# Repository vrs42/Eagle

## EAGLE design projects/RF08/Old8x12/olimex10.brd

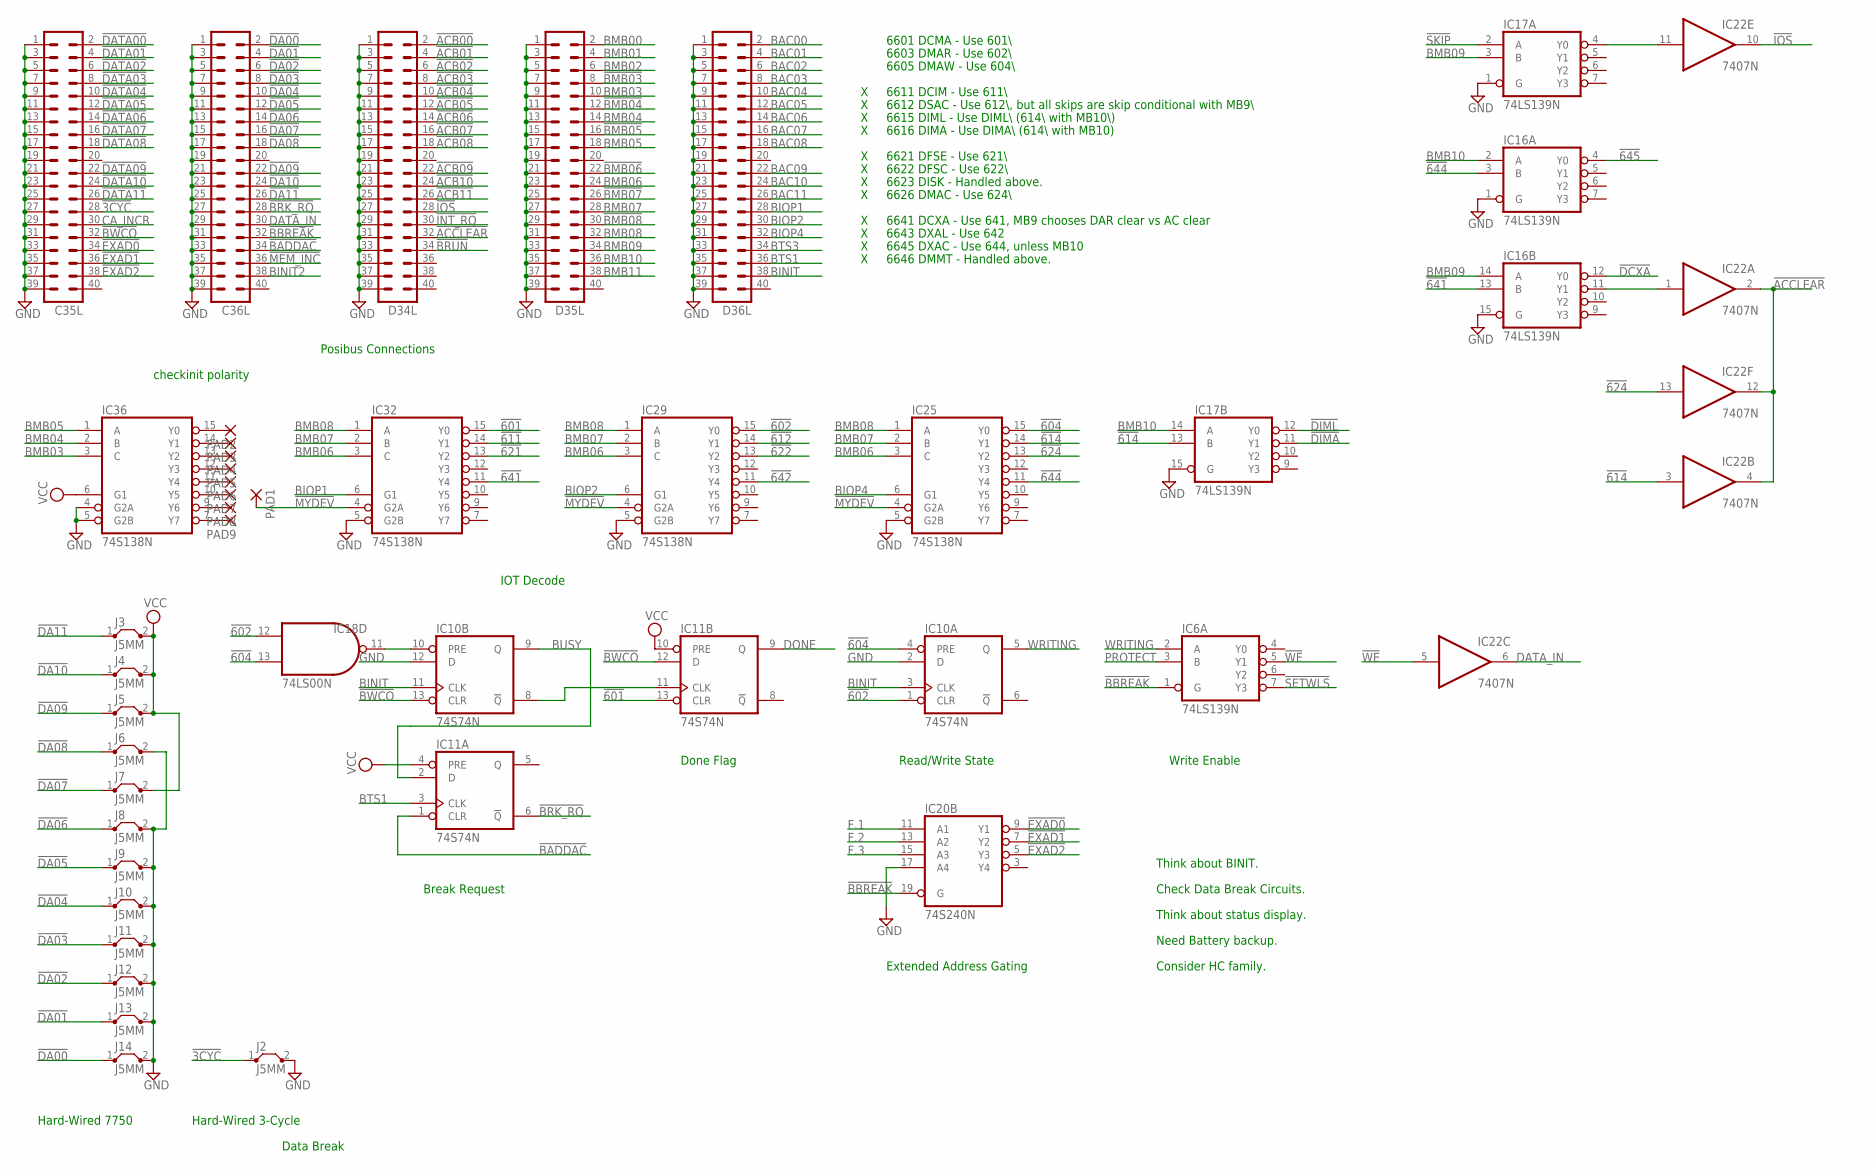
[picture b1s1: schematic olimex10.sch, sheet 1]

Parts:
C35L, C36L: MA20-2
D34L, D35L, D36L: MA20-2
IC6, IC16, IC17: 74LS139N; DIL16
IC10, IC11: 74S74N; DIL14
IC18: 74LS00N; DIL14
IC20: 74S240N; DIL20
IC22: 7407N; DIL14
IC25, IC29, IC32, IC36: 74S138N; DIL16
J2, J3, J4, J5, J6, J7, J8, J9, J10, J11, J12, J13, J14: J5MM; 05
PAD1, PAD2, PAD3, PAD4, PAD5, PAD6, PAD7, PAD8, PAD9: 1,6/0,8

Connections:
!3CYC: C35L.28, J2.1
!601: IC11.13 (CLR), IC32.15 (Y0); also elsewhere on the board
!602: IC10.1 (CLR), IC18.12 (I0), IC29.15 (Y0); also elsewhere on the board
!604: IC10.4 (PRE), IC18.13 (I1), IC25.15 (Y0); also elsewhere on the board
!611: IC32.14 (Y1); also elsewhere on the board
!612: IC29.14 (Y1); also elsewhere on the board
!614: IC17.13 (B), IC22.3 (I), IC25.14 (Y1)
!621: IC32.13 (Y2); also elsewhere on the board
!622: IC29.13 (Y2); also elsewhere on the board
!624: IC22.13 (I), IC25.13 (Y2); also elsewhere on the board
!641: IC16.13 (B), IC32.11 (Y4)
!642: IC29.11 (Y4); also elsewhere on the board
!644: IC16.3 (B), IC25.11 (Y4)
!645: IC16.4 (Y0); also elsewhere on the board
!ACB00: D34L.2; also elsewhere on the board
!ACB01: D34L.4; also elsewhere on the board
!ACB02: D34L.6; also elsewhere on the board
!ACB03: D34L.8; also elsewhere on the board
!ACB04: D34L.10; also elsewhere on the board
!ACB05: D34L.12; also elsewhere on the board
!ACB06: D34L.14; also elsewhere on the board
!ACB07: D34L.16; also elsewhere on the board
!ACB08: D34L.18; also elsewhere on the board
!ACB09: D34L.22; also elsewhere on the board
!ACB10: D34L.24; also elsewhere on the board
!ACB11: D34L.26; also elsewhere on the board
!ACCLEAR: D34L.32, IC22.2 (O), IC22.4 (O), IC22.12 (O)
!BADDAC: C36L.34, IC11.1 (CLR)
!BBREAK: C36L.32, IC6.1 (G), IC20.19 (G); also elsewhere on the board
!BMB03: D35L.8
!BMB04: D35L.12
!BMB05: D35L.16
!BMB06: D35L.22
!BMB07: D35L.26
!BMB08: D35L.30
!BRK_RQ: C36L.28, IC11.6 (!Q); also elsewhere on the board
!BRUN: D34L.34
!BWCO: C35L.32, IC10.13 (CLR), IC11.12 (D); also elsewhere on the board
!DA00: C36L.2, J14.1
!DA01: C36L.4, J13.1
!DA02: C36L.6, J12.1
!DA03: C36L.8, J11.1
!DA04: C36L.10, J10.1
!DA05: C36L.12, J9.1
!DA06: C36L.14, J8.1
!DA07: C36L.16, J7.1
!DA08: C36L.18, J6.1
!DA09: C36L.22, J5.1
!DA10: C36L.24, J4.1
!DA11: C36L.26, J3.1
!DATA00: C35L.2; also elsewhere on the board
!DATA01: C35L.4; also elsewhere on the board
!DATA02: C35L.6; also elsewhere on the board
!DATA03: C35L.8; also elsewhere on the board
!DATA04: C35L.10; also elsewhere on the board
!DATA05: C35L.12; also elsewhere on the board
!DATA06: C35L.14; also elsewhere on the board
!DATA07: C35L.16; also elsewhere on the board
!DATA08: C35L.18; also elsewhere on the board
!DATA09: C35L.22; also elsewhere on the board
!DATA10: C35L.24; also elsewhere on the board
!DATA11: C35L.26; also elsewhere on the board
!DCXA: IC16.12 (Y0); also elsewhere on the board
!DIMA: IC17.11 (Y1); also elsewhere on the board
!DIML: IC17.12 (Y0); also elsewhere on the board
!EXAD0: C35L.34, IC20.9 (Y1)
!EXAD1: C35L.36, IC20.7 (Y2)
!EXAD2: C35L.38, IC20.5 (Y3)
!INT_RQ: D34L.30; also elsewhere on the board
!IOS: D34L.28, IC22.10 (O)
!MEM_INC: C36L.36
!MYDEV: IC25.4 (G2A), IC29.4 (G2A), IC32.4 (G2A), PAD1.1
!SETWLS: IC6.7 (Y3); also elsewhere on the board
!SKIP: IC17.2 (A); also elsewhere on the board
!WE: IC6.5 (Y1), IC22.5 (I); also elsewhere on the board
BAC00: D36L.2; also elsewhere on the board
BAC01: D36L.4; also elsewhere on the board
BAC02: D36L.6; also elsewhere on the board
BAC03: D36L.8; also elsewhere on the board
BAC04: D36L.10; also elsewhere on the board
BAC05: D36L.12; also elsewhere on the board
BAC06: D36L.14; also elsewhere on the board
BAC07: D36L.16; also elsewhere on the board
BAC08: D36L.18; also elsewhere on the board
BAC09: D36L.22; also elsewhere on the board
BAC10: D36L.24; also elsewhere on the board
BAC11: D36L.26; also elsewhere on the board
BINIT: D36L.38, IC10.3 (CLK), IC10.11 (CLK); also elsewhere on the board
BINIT2: C36L.38
BIOP1: D36L.28, IC32.6 (G1)
BIOP2: D36L.30, IC29.6 (G1)
BIOP4: D36L.32, IC25.6 (G1)
BMB00: D35L.2; also elsewhere on the board
BMB01: D35L.4; also elsewhere on the board
BMB02: D35L.6; also elsewhere on the board
BMB03: D35L.10, IC36.3 (C); also elsewhere on the board
BMB04: D35L.14, IC36.2 (B); also elsewhere on the board
BMB05: D35L.18, IC36.1 (A); also elsewhere on the board
BMB06: D35L.24, IC25.3 (C), IC29.3 (C), IC32.3 (C); also elsewhere on the board
BMB07: D35L.28, IC25.2 (B), IC29.2 (B), IC32.2 (B); also elsewhere on the board
BMB08: D35L.32, IC25.1 (A), IC29.1 (A), IC32.1 (A); also elsewhere on the board
BMB09: D35L.34, IC16.14 (A), IC17.3 (B); also elsewhere on the board
BMB10: D35L.36, IC16.2 (A), IC17.14 (A); also elsewhere on the board
BMB11: D35L.38; also elsewhere on the board
BTS1: D36L.36, IC11.3 (CLK)
BTS3: D36L.34
BUSY: IC10.9 (Q), IC11.2 (D); also elsewhere on the board
CA_INCR: C35L.30
DATA_IN: C36L.30, IC22.6 (O)
DONE: IC11.9 (Q); also elsewhere on the board
F.1: IC20.11 (A1); also elsewhere on the board
F.2: IC20.13 (A2); also elsewhere on the board
F.3: IC20.15 (A3); also elsewhere on the board
GND: C35L.1, C35L.3, C35L.5, C35L.7, C35L.9, C35L.11, C35L.13, C35L.15, C35L.17, C35L.19, C35L.21, C35L.23, C35L.25, C35L.27, C35L.29, C35L.31, C35L.33, C35L.35, C35L.37, C35L.39, C36L.1, C36L.3, C36L.5, C36L.7, C36L.9, C36L.11, C36L.13, C36L.15, C36L.17, C36L.19, C36L.21, C36L.23, C36L.25, C36L.27, C36L.29, C36L.31, C36L.33, C36L.35, C36L.37, C36L.39, D34L.1, D34L.3, D34L.5, D34L.7, D34L.9, D34L.11, D34L.13, D34L.15, D34L.17, D34L.19, D34L.21, D34L.23, D34L.25, D34L.27, D34L.29, D34L.31, D34L.33, D34L.35, D34L.37, D34L.39, D35L.1, D35L.3, D35L.5, D35L.7, D35L.9, D35L.11, D35L.13, D35L.15, D35L.17, D35L.19, D35L.21, D35L.23, D35L.25, D35L.27, D35L.29, D35L.31, D35L.33, D35L.35, D35L.37, D35L.39, D36L.1, D36L.3, D36L.5, D36L.7, D36L.9, D36L.11, D36L.13, D36L.15, D36L.17, D36L.19, D36L.21, D36L.23, D36L.25, D36L.27, D36L.29, D36L.31, D36L.33, D36L.35, D36L.37, D36L.39, IC6.8 (GND), IC10.2 (D), IC10.7 (GND), IC10.12 (D), IC11.7 (GND), IC16.1 (G), IC16.8 (GND), IC16.15 (G), IC17.1 (G), IC17.8 (GND), IC17.15 (G), IC18.7 (GND), IC20.10 (GND), IC20.17 (A4), IC22.7 (GND), IC25.5 (G2B), IC25.8 (GND), IC29.5 (G2B), IC29.8 (GND), IC32.5 (G2B), IC32.8 (GND), IC36.4 (G2A), IC36.5 (G2B), IC36.8 (GND), J2.2, J6.2, J8.2, J9.2, J10.2, J11.2, J12.2, J13.2, J14.2; also elsewhere on the board
unnamed: IC36.9 (Y6), PAD8.1
unnamed: IC10.8 (!Q), IC11.11 (CLK)
unnamed: IC36.15 (Y0), PAD2.1
unnamed: IC36.14 (Y1), PAD3.1
unnamed: IC36.13 (Y2), PAD4.1
unnamed: IC36.12 (Y3), PAD5.1
unnamed: IC36.11 (Y4), PAD6.1
unnamed: IC36.10 (Y5), PAD7.1
unnamed: IC36.7 (Y7), PAD9.1
unnamed: IC16.11 (Y1), IC22.1 (I)
unnamed: IC17.4 (Y0), IC22.11 (I)
unnamed: IC10.10 (PRE), IC18.11 (O)
PROTECT: IC6.3 (B); also elsewhere on the board
VCC: IC6.16 (VCC), IC10.14 (VCC), IC11.4 (PRE), IC11.10 (PRE), IC11.14 (VCC), IC16.16 (VCC), IC17.16 (VCC), IC18.14 (VCC), IC20.20 (VCC), IC22.14 (VCC), IC25.16 (VCC), IC29.16 (VCC), IC32.16 (VCC), IC36.6 (G1), IC36.16 (VCC), J3.2, J4.2, J5.2, J7.2; also elsewhere on the board
WRITING: IC6.2 (A), IC10.5 (Q); also elsewhere on the board

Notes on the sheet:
6601 DCMA - Use 601\\
6603 DMAR - Use 602\\
6605 DMAW - Use 604\\
6611 DCIM - Use 611\\
6612 DSAC - Use 612\\, but all skips are skip conditional with MB9\\
6615 DIML - Use DIML\\ (614\\ with MB10\\)
6616 DIMA - Use DIMA\\ (614\\ with MB10)
6621 DFSE - Use 621\\
6622 DFSC - Use 622\\
6623 DISK - Handled above.
6626 DMAC - Use 624\\
6641 DCXA - Use 641, MB9 chooses DAR clear vs AC clear
6643 DXAL - Use 642
6645 DXAC - Use 644, unless MB10
6646 DMMT - Handled above.
Posibus Connections
IOT Decode
Data Break
Hard-Wired 7750
Hard-Wired 3-Cycle
Think about BINIT.
Think about status display.
Break Request
Need Battery backup.
Done Flag
Extended Address Gating
Read/Write State
Write Enable
Check Data Break Circuits.
Consider HC family.
checkinit polarity

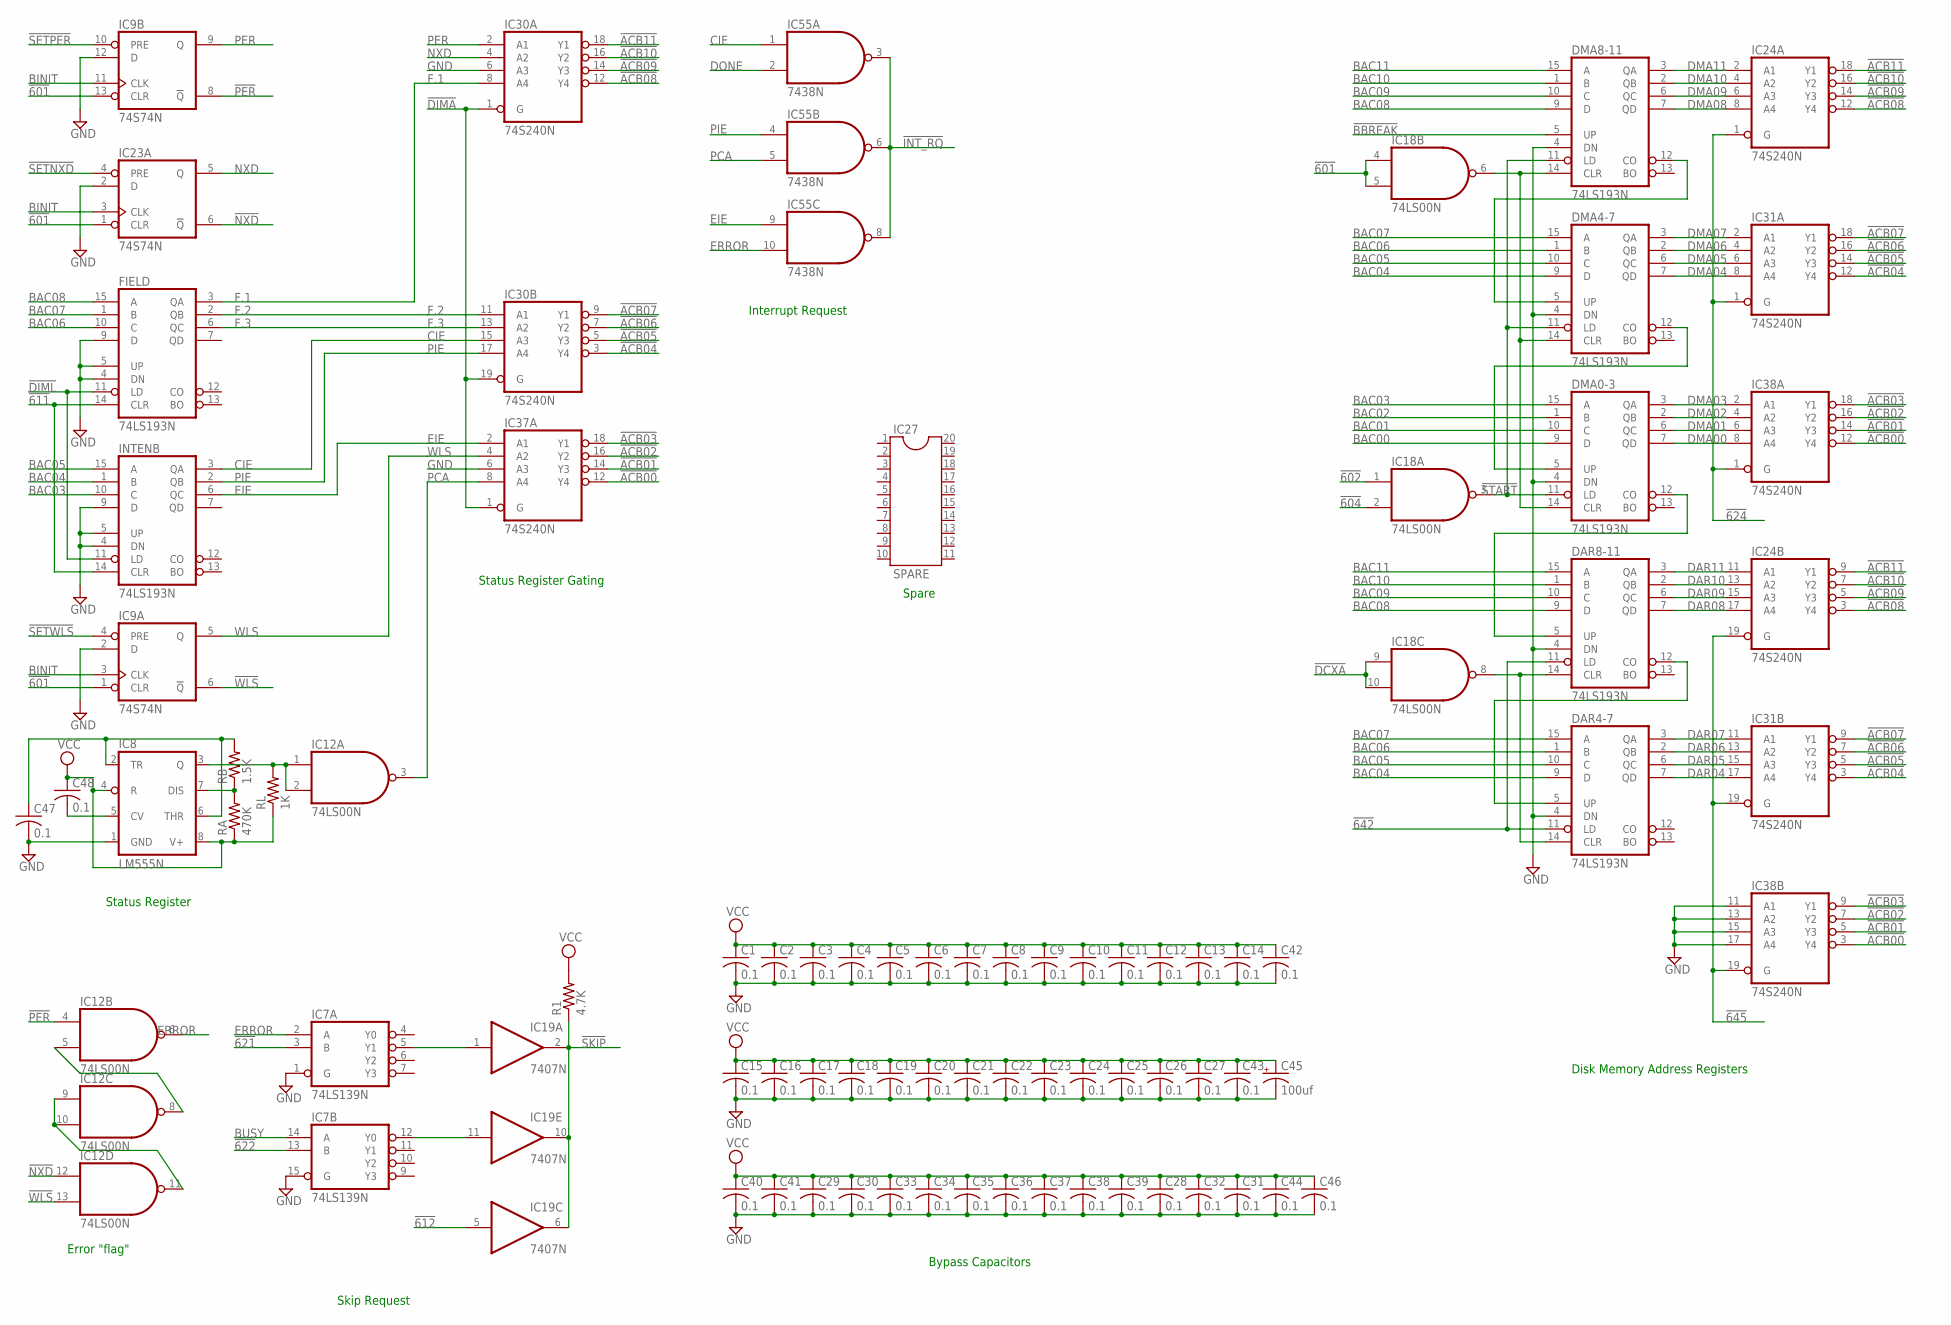
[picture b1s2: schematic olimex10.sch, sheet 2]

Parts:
C1, C2, C3, C4, C5, C6, C7, C8, C9, C10, C11, C12, C13, C14, C15, C16, C17, C18, C19, C20, C21, C22, C23, C24, C25, C26, C27, C28, C29, C30, C31, C32, C33, C34, C35, C36, C37, C38, C39, C40, C41, C42, C43, C44, C46, C47, C48: 0.1; C050-025X075
C45: 100uf; E22-6
DAR4-7, DAR8-11: 74LS193N; DIL16
DMA0-3, DMA4-7, DMA8-11: 74LS193N; DIL16
FIELD: 74LS193N; DIL16
IC7: 74LS139N; DIL16
IC8: LM555N; DIL08
IC9, IC23: 74S74N; DIL14
IC12, IC18: 74LS00N; DIL14
IC19: 7407N; DIL14
IC24, IC30, IC31, IC37, IC38: 74S240N; DIL20
IC27: SPARE; DIL20
IC55: 7438N; DIL14
INTENB: 74LS193N; DIL16
R1: 4.7K; 0207/10
RA: 470K; 0207/10
RB: 1.5K; 0207/10
RL: 1K; 0207/10

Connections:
!601: IC9.1 (CLR), IC9.13 (CLR), IC18.4 (I0), IC18.5 (I1), IC23.1 (CLR); also elsewhere on the board
!602: IC18.1 (I0); also elsewhere on the board
!604: IC18.2 (I1); also elsewhere on the board
!611: FIELD.14 (CLR), INTENB.14 (CLR); also elsewhere on the board
!612: IC19.5 (I); also elsewhere on the board
!621: IC7.3 (B); also elsewhere on the board
!622: IC7.13 (B); also elsewhere on the board
!624: IC24.1 (G), IC31.1 (G), IC38.1 (G); also elsewhere on the board
!642: DAR4-7.11 (LD), DAR8-11.11 (LD); also elsewhere on the board
!645: IC24.19 (G), IC31.19 (G), IC38.19 (G); also elsewhere on the board
!ACB00: IC37.12 (Y4), IC38.3 (Y4), IC38.12 (Y4); also elsewhere on the board
!ACB01: IC37.14 (Y3), IC38.5 (Y3), IC38.14 (Y3); also elsewhere on the board
!ACB02: IC37.16 (Y2), IC38.7 (Y2), IC38.16 (Y2); also elsewhere on the board
!ACB03: IC37.18 (Y1), IC38.9 (Y1), IC38.18 (Y1); also elsewhere on the board
!ACB04: IC30.3 (Y4), IC31.3 (Y4), IC31.12 (Y4); also elsewhere on the board
!ACB05: IC30.5 (Y3), IC31.5 (Y3), IC31.14 (Y3); also elsewhere on the board
!ACB06: IC30.7 (Y2), IC31.7 (Y2), IC31.16 (Y2); also elsewhere on the board
!ACB07: IC30.9 (Y1), IC31.9 (Y1), IC31.18 (Y1); also elsewhere on the board
!ACB08: IC24.3 (Y4), IC24.12 (Y4), IC30.12 (Y4); also elsewhere on the board
!ACB09: IC24.5 (Y3), IC24.14 (Y3), IC30.14 (Y3); also elsewhere on the board
!ACB10: IC24.7 (Y2), IC24.16 (Y2), IC30.16 (Y2); also elsewhere on the board
!ACB11: IC24.9 (Y1), IC24.18 (Y1), IC30.18 (Y1); also elsewhere on the board
!BBREAK: DMA8-11.5 (UP); also elsewhere on the board
!DCXA: IC18.9 (I0), IC18.10 (I1); also elsewhere on the board
!DIMA: IC30.1 (G), IC30.19 (G), IC37.1 (G); also elsewhere on the board
!DIML: FIELD.11 (LD), INTENB.11 (LD); also elsewhere on the board
!INT_RQ: IC55.3 (O), IC55.6 (O), IC55.8 (O); also elsewhere on the board
!NXD: IC12.12 (I0), IC23.6 (!Q)
!PER: IC9.8 (!Q), IC12.4 (I0)
!SETNXD: IC23.4 (PRE); also elsewhere on the board
!SETPER: IC9.10 (PRE); also elsewhere on the board
!SETWLS: IC9.4 (PRE); also elsewhere on the board
!SKIP: IC19.2 (O), IC19.6 (O), IC19.10 (O), R1.1; also elsewhere on the board
!START: DMA0-3.11 (LD), DMA4-7.11 (LD), DMA8-11.11 (LD), IC18.3 (O)
!WLS: IC9.6 (!Q), IC12.13 (I1)
BAC00: DMA0-3.9 (D); also elsewhere on the board
BAC01: DMA0-3.10 (C); also elsewhere on the board
BAC02: DMA0-3.1 (B); also elsewhere on the board
BAC03: DMA0-3.15 (A), INTENB.10 (C); also elsewhere on the board
BAC04: DAR4-7.9 (D), DMA4-7.9 (D), INTENB.1 (B); also elsewhere on the board
BAC05: DAR4-7.10 (C), DMA4-7.10 (C), INTENB.15 (A); also elsewhere on the board
BAC06: DAR4-7.1 (B), DMA4-7.1 (B), FIELD.10 (C); also elsewhere on the board
BAC07: DAR4-7.15 (A), DMA4-7.15 (A), FIELD.1 (B); also elsewhere on the board
BAC08: DAR8-11.9 (D), DMA8-11.9 (D), FIELD.15 (A); also elsewhere on the board
BAC09: DAR8-11.10 (C), DMA8-11.10 (C); also elsewhere on the board
BAC10: DAR8-11.1 (B), DMA8-11.1 (B); also elsewhere on the board
BAC11: DAR8-11.15 (A), DMA8-11.15 (A); also elsewhere on the board
BINIT: IC9.3 (CLK), IC9.11 (CLK), IC23.3 (CLK); also elsewhere on the board
BUSY: IC7.14 (A); also elsewhere on the board
CIE: IC30.15 (A3), IC55.1 (I0), INTENB.3 (QA); also elsewhere on the board
DAR04: DAR4-7.7 (QD), IC31.17 (A4); also elsewhere on the board
DAR05: DAR4-7.6 (QC), IC31.15 (A3); also elsewhere on the board
DAR06: DAR4-7.2 (QB), IC31.13 (A2); also elsewhere on the board
DAR07: DAR4-7.3 (QA), IC31.11 (A1); also elsewhere on the board
DAR08: DAR8-11.7 (QD), IC24.17 (A4); also elsewhere on the board
DAR09: DAR8-11.6 (QC), IC24.15 (A3); also elsewhere on the board
DAR10: DAR8-11.2 (QB), IC24.13 (A2); also elsewhere on the board
DAR11: DAR8-11.3 (QA), IC24.11 (A1); also elsewhere on the board
DMA00: DMA0-3.7 (QD), IC38.8 (A4); also elsewhere on the board
DMA01: DMA0-3.6 (QC), IC38.6 (A3); also elsewhere on the board
DMA02: DMA0-3.2 (QB), IC38.4 (A2); also elsewhere on the board
DMA03: DMA0-3.3 (QA), IC38.2 (A1); also elsewhere on the board
DMA04: DMA4-7.7 (QD), IC31.8 (A4); also elsewhere on the board
DMA05: DMA4-7.6 (QC), IC31.6 (A3); also elsewhere on the board
DMA06: DMA4-7.2 (QB), IC31.4 (A2); also elsewhere on the board
DMA07: DMA4-7.3 (QA), IC31.2 (A1); also elsewhere on the board
DMA08: DMA8-11.7 (QD), IC24.8 (A4); also elsewhere on the board
DMA09: DMA8-11.6 (QC), IC24.6 (A3); also elsewhere on the board
DMA10: DMA8-11.2 (QB), IC24.4 (A2); also elsewhere on the board
DMA11: DMA8-11.3 (QA), IC24.2 (A1); also elsewhere on the board
DONE: IC55.2 (I1); also elsewhere on the board
EIE: IC37.2 (A1), IC55.9 (I0), INTENB.6 (QC); also elsewhere on the board
ERROR: IC7.2 (A), IC12.6 (O), IC55.10 (I1)
F.1: FIELD.3 (QA), IC30.8 (A4); also elsewhere on the board
F.2: FIELD.2 (QB), IC30.11 (A1); also elsewhere on the board
F.3: FIELD.6 (QC), IC30.13 (A2); also elsewhere on the board
GND: C1.2, C2.2, C3.2, C4.2, C5.2, C6.2, C7.2, C8.2, C9.2, C10.2, C11.2, C12.2, C13.2, C14.2, C15.2, C16.2, C17.2, C18.2, C19.2, C20.2, C21.2, C22.2, C23.2, C24.2, C25.2, C26.2, C27.2, C28.2, C29.2, C30.2, C31.2, C32.2, C33.2, C34.2, C35.2, C36.2, C37.2, C38.2, C39.2, C40.2, C41.2, C42.2, C43.2, C44.2, C45.-, C46.2, C47.2, DAR4-7.4 (DN), DAR4-7.8 (GND), DAR8-11.4 (DN), DAR8-11.8 (GND), DMA0-3.4 (DN), DMA0-3.8 (GND), DMA4-7.4 (DN), DMA4-7.8 (GND), DMA8-11.4 (DN), DMA8-11.8 (GND), FIELD.4 (DN), FIELD.5 (UP), FIELD.8 (GND), FIELD.9 (D), IC7.1 (G), IC7.8 (GND), IC7.15 (G), IC8.1 (GND), IC9.2 (D), IC9.7 (GND), IC9.12 (D), IC12.7 (GND), IC18.7 (GND), IC19.7 (GND), IC23.2 (D), IC23.7 (GND), IC24.10 (GND), IC30.6 (A3), IC30.10 (GND), IC31.10 (GND), IC37.6 (A3), IC37.10 (GND), IC38.10 (GND), IC38.11 (A1), IC38.13 (A2), IC38.15 (A3), IC38.17 (A4), IC55.7 (GND), INTENB.4 (DN), INTENB.5 (UP), INTENB.8 (GND), INTENB.9 (D); also elsewhere on the board
unnamed: DMA0-3.5 (UP), DMA4-7.12 (CO)
unnamed: DAR4-7.14 (CLR), DAR8-11.14 (CLR), IC18.8 (O)
unnamed: DMA4-7.5 (UP), DMA8-11.12 (CO)
unnamed: DAR8-11.5 (UP), DMA0-3.12 (CO)
unnamed: DMA0-3.14 (CLR), DMA4-7.14 (CLR), DMA8-11.14 (CLR), IC18.6 (O)
unnamed: DAR4-7.5 (UP), DAR8-11.12 (CO)
unnamed: IC7.5 (Y1), IC19.1 (I)
unnamed: IC8.7 (DIS), RA.2, RB.1
unnamed: IC8.3 (Q), IC12.1 (I0), IC12.2 (I1), RL.2
unnamed: C47.1, IC8.2 (TR), IC8.6 (THR), RB.2
unnamed: IC7.12 (Y0), IC19.11 (I)
unnamed: C48.2, IC8.5 (CV)
unnamed: IC12.9 (I0), IC12.10 (I1), IC12.11 (O)
unnamed: IC12.5 (I1), IC12.8 (O)
NXD: IC23.5 (Q), IC30.4 (A2); also elsewhere on the board
PCA: IC12.3 (O), IC37.8 (A4), IC55.5 (I1)
PER: IC9.9 (Q), IC30.2 (A1); also elsewhere on the board
PIE: IC30.17 (A4), IC55.4 (I0), INTENB.2 (QB); also elsewhere on the board
VCC: C1.1, C2.1, C3.1, C4.1, C5.1, C6.1, C7.1, C8.1, C9.1, C10.1, C11.1, C12.1, C13.1, C14.1, C15.1, C16.1, C17.1, C18.1, C19.1, C20.1, C21.1, C22.1, C23.1, C24.1, C25.1, C26.1, C27.1, C28.1, C29.1, C30.1, C31.1, C32.1, C33.1, C34.1, C35.1, C36.1, C37.1, C38.1, C39.1, C40.1, C41.1, C42.1, C43.1, C44.1, C45.+, C46.1, C48.1, DAR4-7.16 (VCC), DAR8-11.16 (VCC), DMA0-3.16 (VCC), DMA4-7.16 (VCC), DMA8-11.16 (VCC), FIELD.16 (VCC), IC7.16 (VCC), IC8.4 (R), IC8.8 (V+), IC9.14 (VCC), IC12.14 (VCC), IC18.14 (VCC), IC19.14 (VCC), IC23.14 (VCC), IC24.20 (VCC), IC30.20 (VCC), IC31.20 (VCC), IC37.20 (VCC), IC38.20 (VCC), IC55.14 (VCC), INTENB.16 (VCC), R1.2, RA.1, RL.1; also elsewhere on the board
WLS: IC9.5 (Q), IC37.4 (A2); also elsewhere on the board

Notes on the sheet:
Disk Memory Address Registers
Status Register
Status Register Gating
Interrupt Request
Error "flag"
Skip Request
Spare
Bypass Capacitors

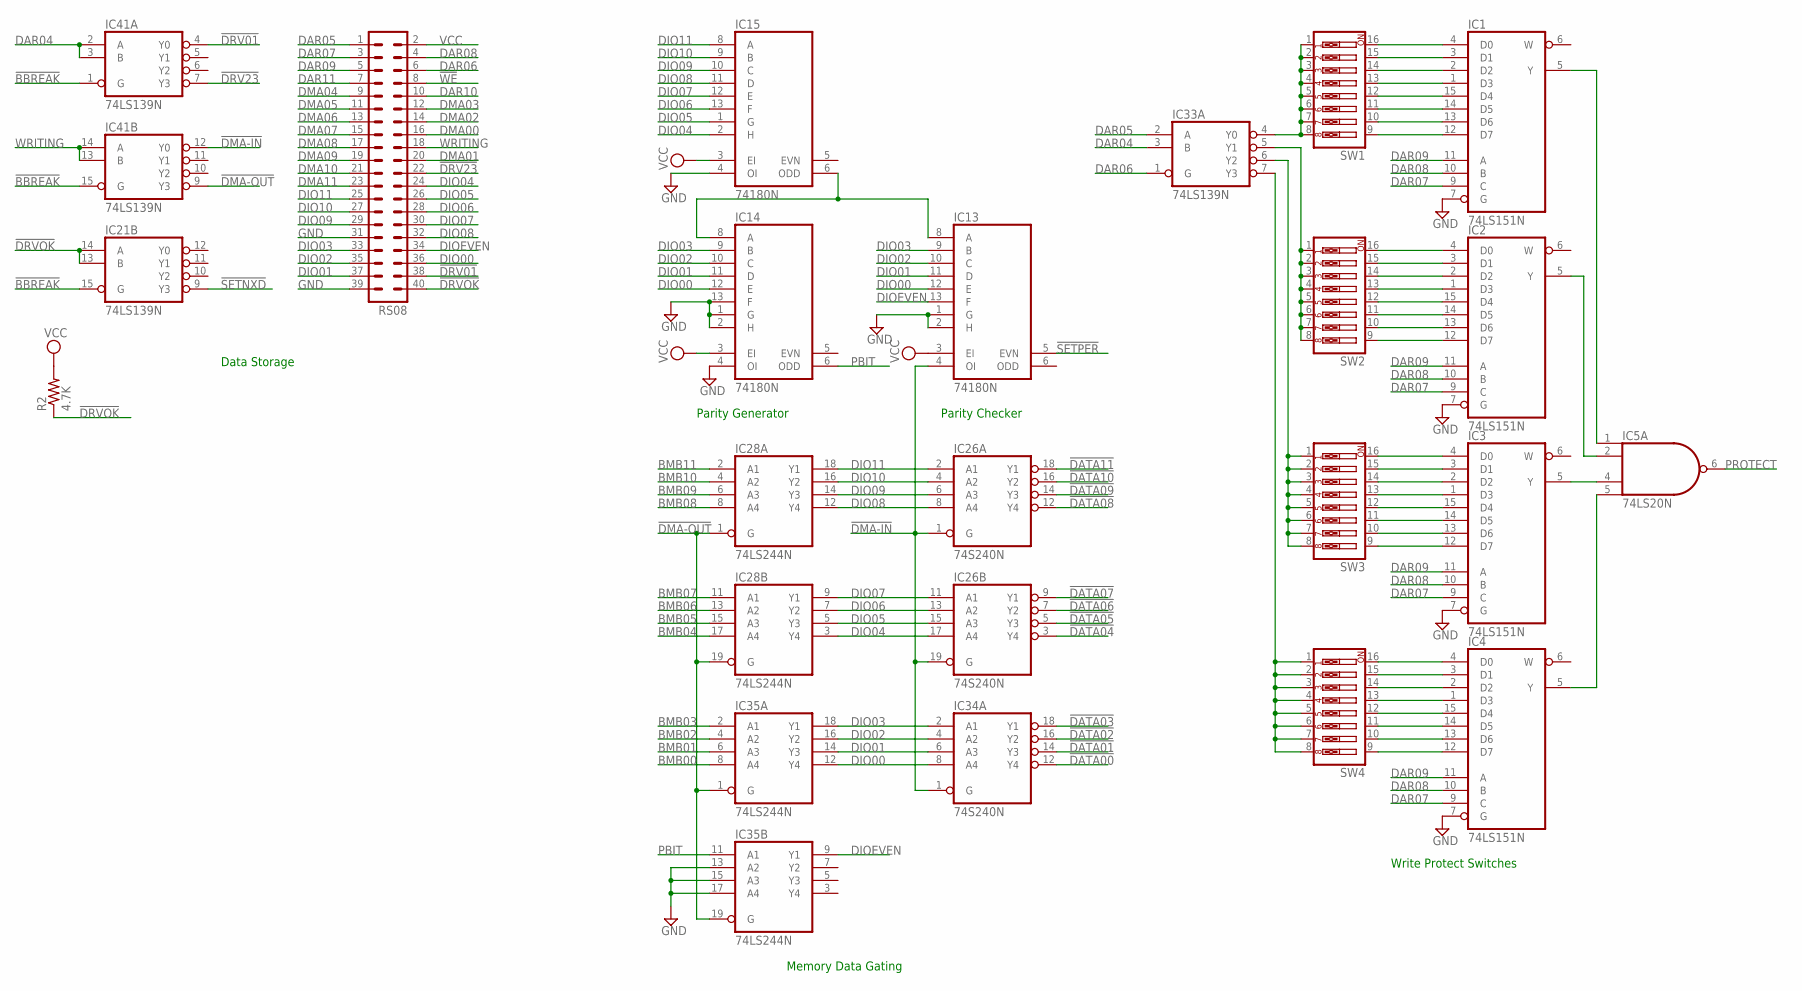
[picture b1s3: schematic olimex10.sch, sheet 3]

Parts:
IC1, IC2, IC3, IC4: 74LS151N; DIL16
IC5: 74LS20N; DIL14
IC13, IC14, IC15: 74180N; DIL14
IC21, IC33, IC41: 74LS139N; DIL16
IC26, IC34: 74S240N; DIL20
IC28, IC35: 74LS244N; DIL20
R2: 4.7K; 0207/10
RS08: MA20-2
SW1, SW2, SW3, SW4: SW_DIP-8; EDG-08

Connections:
!BBREAK: IC21.15 (G), IC41.1 (G), IC41.15 (G); also elsewhere on the board
!DATA00: IC34.12 (Y4); also elsewhere on the board
!DATA01: IC34.14 (Y3); also elsewhere on the board
!DATA02: IC34.16 (Y2); also elsewhere on the board
!DATA03: IC34.18 (Y1); also elsewhere on the board
!DATA04: IC26.3 (Y4); also elsewhere on the board
!DATA05: IC26.5 (Y3); also elsewhere on the board
!DATA06: IC26.7 (Y2); also elsewhere on the board
!DATA07: IC26.9 (Y1); also elsewhere on the board
!DATA08: IC26.12 (Y4); also elsewhere on the board
!DATA09: IC26.14 (Y3); also elsewhere on the board
!DATA10: IC26.16 (Y2); also elsewhere on the board
!DATA11: IC26.18 (Y1); also elsewhere on the board
!DMA-IN: IC13.4 (OI), IC26.1 (G), IC26.19 (G), IC34.1 (G), IC41.12 (Y0)
!DMA-OUT: IC28.1 (G), IC28.19 (G), IC35.1 (G), IC35.19 (G), IC41.9 (Y3)
!DRV01: IC41.4 (Y0), RS08.38; also elsewhere on the board
!DRV23: IC41.7 (Y3), RS08.22; also elsewhere on the board
!DRVOK: IC21.13 (B), IC21.14 (A), R2.1, RS08.40; also elsewhere on the board
!SETNXD: IC21.9 (Y3); also elsewhere on the board
!SETPER: IC13.5 (EVN); also elsewhere on the board
!WE: RS08.8; also elsewhere on the board
BMB00: IC35.8 (A4); also elsewhere on the board
BMB01: IC35.6 (A3); also elsewhere on the board
BMB02: IC35.4 (A2); also elsewhere on the board
BMB03: IC35.2 (A1); also elsewhere on the board
BMB04: IC28.17 (A4); also elsewhere on the board
BMB05: IC28.15 (A3); also elsewhere on the board
BMB06: IC28.13 (A2); also elsewhere on the board
BMB07: IC28.11 (A1); also elsewhere on the board
BMB08: IC28.8 (A4); also elsewhere on the board
BMB09: IC28.6 (A3); also elsewhere on the board
BMB10: IC28.4 (A2); also elsewhere on the board
BMB11: IC28.2 (A1); also elsewhere on the board
DAR04: IC33.3 (B), IC41.2 (A), IC41.3 (B); also elsewhere on the board
DAR05: IC33.2 (A), RS08.1; also elsewhere on the board
DAR06: IC33.1 (G), RS08.6; also elsewhere on the board
DAR07: IC1.9 (C), IC2.9 (C), IC3.9 (C), IC4.9 (C), RS08.3; also elsewhere on the board
DAR08: IC1.10 (B), IC2.10 (B), IC3.10 (B), IC4.10 (B), RS08.4; also elsewhere on the board
DAR09: IC1.11 (A), IC2.11 (A), IC3.11 (A), IC4.11 (A), RS08.5; also elsewhere on the board
DAR10: RS08.10; also elsewhere on the board
DAR11: RS08.7; also elsewhere on the board
DIO00: IC13.12 (E), IC14.12 (E), IC34.8 (A4), IC35.12 (Y4), RS08.36; also elsewhere on the board
DIO01: IC13.11 (D), IC14.11 (D), IC34.6 (A3), IC35.14 (Y3), RS08.37; also elsewhere on the board
DIO02: IC13.10 (C), IC14.10 (C), IC34.4 (A2), IC35.16 (Y2), RS08.35; also elsewhere on the board
DIO03: IC13.9 (B), IC14.9 (B), IC34.2 (A1), IC35.18 (Y1), RS08.33; also elsewhere on the board
DIO04: IC15.2 (H), IC26.17 (A4), IC28.3 (Y4), RS08.24; also elsewhere on the board
DIO05: IC15.1 (G), IC26.15 (A3), IC28.5 (Y3), RS08.26; also elsewhere on the board
DIO06: IC15.13 (F), IC26.13 (A2), IC28.7 (Y2), RS08.28; also elsewhere on the board
DIO07: IC15.12 (E), IC26.11 (A1), IC28.9 (Y1), RS08.30; also elsewhere on the board
DIO08: IC15.11 (D), IC26.8 (A4), IC28.12 (Y4), RS08.32; also elsewhere on the board
DIO09: IC15.10 (C), IC26.6 (A3), IC28.14 (Y3), RS08.29; also elsewhere on the board
DIO10: IC15.9 (B), IC26.4 (A2), IC28.16 (Y2), RS08.27; also elsewhere on the board
DIO11: IC15.8 (A), IC26.2 (A1), IC28.18 (Y1), RS08.25; also elsewhere on the board
DIOEVEN: IC13.13 (F), IC35.9 (Y1), RS08.34; also elsewhere on the board
DMA00: RS08.16; also elsewhere on the board
DMA01: RS08.20; also elsewhere on the board
DMA02: RS08.14; also elsewhere on the board
DMA03: RS08.12; also elsewhere on the board
DMA04: RS08.9; also elsewhere on the board
DMA05: RS08.11; also elsewhere on the board
DMA06: RS08.13; also elsewhere on the board
DMA07: RS08.15; also elsewhere on the board
DMA08: RS08.17; also elsewhere on the board
DMA09: RS08.19; also elsewhere on the board
DMA10: RS08.21; also elsewhere on the board
DMA11: RS08.23; also elsewhere on the board
GND: IC1.7 (G), IC1.8 (GND), IC2.7 (G), IC2.8 (GND), IC3.7 (G), IC3.8 (GND), IC4.7 (G), IC4.8 (GND), IC5.7 (GND), IC13.1 (G), IC13.2 (H), IC13.7 (GND), IC14.1 (G), IC14.2 (H), IC14.4 (OI), IC14.7 (GND), IC14.13 (F), IC15.4 (OI), IC15.7 (GND), IC21.8 (GND), IC26.10 (GND), IC28.10 (GND), IC33.8 (GND), IC34.10 (GND), IC35.10 (GND), IC35.13 (A2), IC35.15 (A3), IC35.17 (A4), IC41.8 (GND), RS08.31, RS08.39; also elsewhere on the board
unnamed: IC33.4 (Y0), SW1.1, SW1.2, SW1.3, SW1.4, SW1.5, SW1.6, SW1.7, SW1.8
unnamed: IC13.8 (A), IC14.8 (A), IC15.6 (ODD)
unnamed: IC2.5 (Y), IC5.2 (I1)
unnamed: IC33.5 (Y1), SW2.1, SW2.2, SW2.3, SW2.4, SW2.5, SW2.6, SW2.7, SW2.8
unnamed: IC33.6 (Y2), SW3.1, SW3.2, SW3.3, SW3.4, SW3.5, SW3.6, SW3.7, SW3.8
unnamed: IC33.7 (Y3), SW4.1, SW4.2, SW4.3, SW4.4, SW4.5, SW4.6, SW4.7, SW4.8
unnamed: IC3.5 (Y), IC5.4 (I2)
unnamed: IC1.5 (Y), IC5.1 (I0)
unnamed: IC4.5 (Y), IC5.5 (I3)
unnamed: IC1.4 (D0), SW1.16
unnamed: IC1.3 (D1), SW1.15
unnamed: IC1.2 (D2), SW1.14
unnamed: IC1.1 (D3), SW1.13
unnamed: IC1.14 (D5), SW1.11
unnamed: IC1.13 (D6), SW1.10
unnamed: IC1.12 (D7), SW1.9
unnamed: IC1.15 (D4), SW1.12
unnamed: IC2.4 (D0), SW2.16
unnamed: IC2.3 (D1), SW2.15
unnamed: IC2.2 (D2), SW2.14
unnamed: IC2.1 (D3), SW2.13
unnamed: IC2.14 (D5), SW2.11
unnamed: IC2.13 (D6), SW2.10
unnamed: IC2.12 (D7), SW2.9
unnamed: IC3.4 (D0), SW3.16
unnamed: IC3.3 (D1), SW3.15
unnamed: IC3.2 (D2), SW3.14
unnamed: IC3.1 (D3), SW3.13
unnamed: IC3.14 (D5), SW3.11
unnamed: IC3.13 (D6), SW3.10
unnamed: IC3.12 (D7), SW3.9
unnamed: IC4.4 (D0), SW4.16
unnamed: IC4.3 (D1), SW4.15
unnamed: IC4.2 (D2), SW4.14
unnamed: IC4.1 (D3), SW4.13
unnamed: IC4.14 (D5), SW4.11
unnamed: IC4.13 (D6), SW4.10
unnamed: IC4.12 (D7), SW4.9
unnamed: IC4.15 (D4), SW4.12
unnamed: IC3.15 (D4), SW3.12
unnamed: IC2.15 (D4), SW2.12
PBIT: IC14.6 (ODD), IC35.11 (A1)
PROTECT: IC5.6 (O); also elsewhere on the board
VCC: IC1.16 (VCC), IC2.16 (VCC), IC3.16 (VCC), IC4.16 (VCC), IC5.14 (VCC), IC13.3 (EI), IC13.14 (VCC), IC14.3 (EI), IC14.14 (VCC), IC15.3 (EI), IC15.14 (VCC), IC21.16 (VCC), IC26.20 (VCC), IC28.20 (VCC), IC33.16 (VCC), IC34.20 (VCC), IC35.20 (VCC), IC41.16 (VCC), R2.2, RS08.2; also elsewhere on the board
WRITING: IC41.13 (B), IC41.14 (A), RS08.18; also elsewhere on the board

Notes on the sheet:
Parity Generator
Parity Checker
Memory Data Gating
Write Protect Switches
Data Storage

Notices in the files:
projects/RF08/Old8x12/writelockswitches.brd:
DF32x4 Write Lock Switches (c) 2003 CEMorris
